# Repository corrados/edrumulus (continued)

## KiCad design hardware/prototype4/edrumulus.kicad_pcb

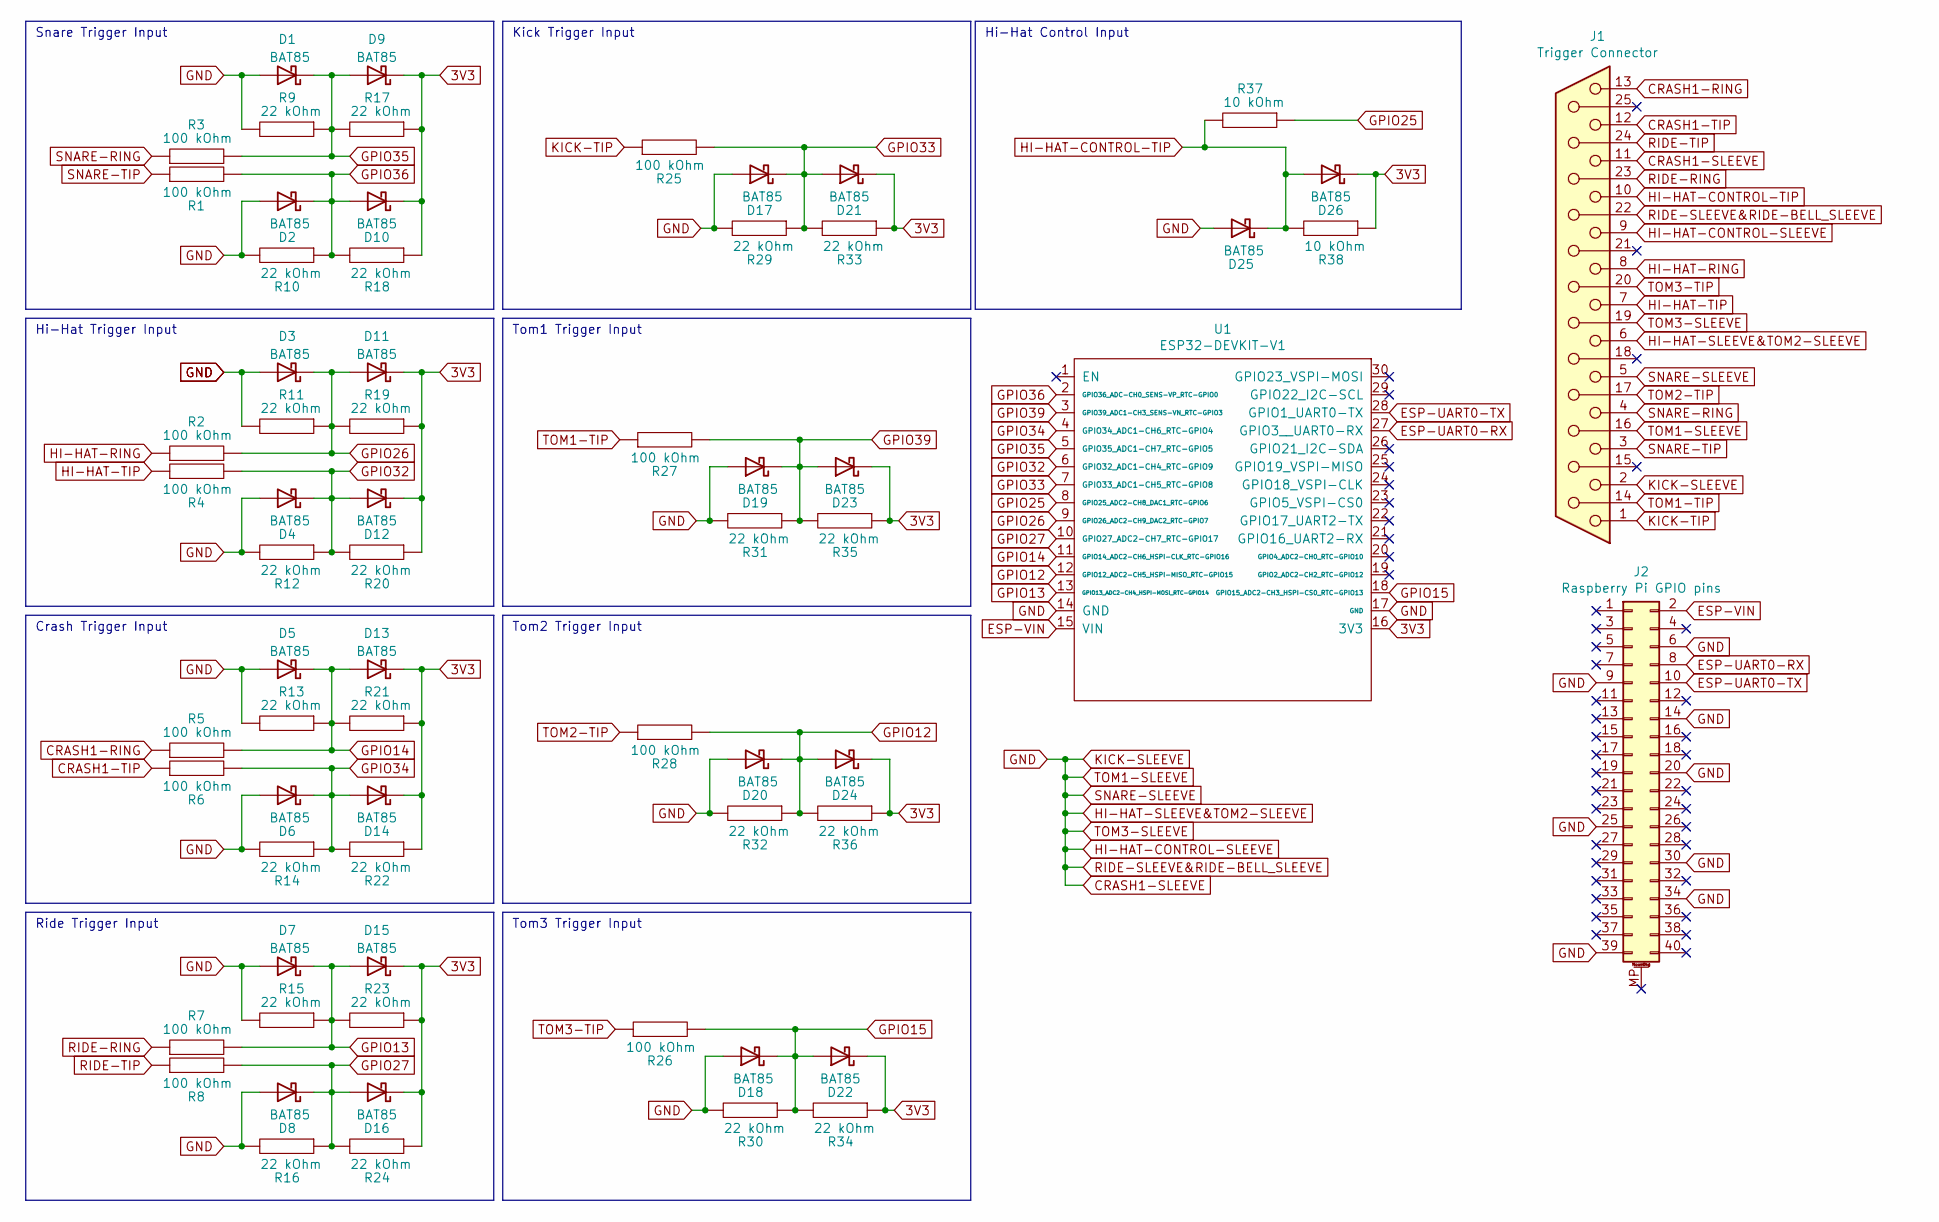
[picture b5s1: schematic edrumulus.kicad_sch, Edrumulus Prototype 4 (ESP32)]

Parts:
D1, D2, D3, D4, D5, D6, D7, D8, D9, D10, D11, D12, D13, D14, D15, D16, D17, D18, D19, D20, D21, D22, D23, D24, D25, D26: BAT85; D_MiniMELF
J1: Trigger Connector; DSUB-25_Female_Vertical_P2.77x2.84mm
J2: Raspberry Pi GPIO pins; PinHeader_2x20_P2.54mm_Vertical
R1, R2, R3, R4, R5, R6, R7, R8, R25, R26, R27, R28: 100 kOhm; R_1206_3216Metric_Pad1.30x1.75mm_HandSolder
R9, R10, R11, R12, R13, R14, R15, R16, R17, R18, R19, R20, R21, R22, R23, R24, R29, R30, R31, R32, R33, R34, R35, R36: 22 kOhm; R_1206_3216Metric_Pad1.30x1.75mm_HandSolder
R37, R38: 10 kOhm; R_1206_3216Metric_Pad1.30x1.75mm_HandSolder
U1: ESP32-DEVKIT-V1; esp32_devkit_v1

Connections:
3V3: D9.1 (K), D10.1 (K), D11.1 (K), D12.1 (K), D13.1 (K), D14.1 (K), D15.1 (K), D16.1 (K), D21.1 (K), D22.1 (K), D23.1 (K), D24.1 (K), D26.1 (K), R17.1, R18.1, R19.1, R20.1, R21.1, R22.1, R23.1, R24.1, R33.1, R34.1, R35.1, R36.1, R38.1, U1.16 (3V3)
CRASH1-RING: J1.13, R5.1
CRASH1-SLEEVE: D1.2 (A), D2.2 (A), D3.2 (A), D4.2 (A), D5.2 (A), D6.2 (A), D7.2 (A), D8.2 (A), D17.2 (A), D18.2 (A), D19.2 (A), D20.2 (A), D25.2 (A), J1.2, J1.5, J1.6, J1.9, J1.11, J1.16, J1.19, J1.22, J2.6, J2.9, J2.14, J2.20, J2.25, J2.30, J2.34, J2.39, R9.2, R10.2, R11.2, R12.2, R13.2, R14.2, R15.2, R16.2, R29.2, R30.2, R31.2, R32.2, U1.14 (GND), U1.17 (GND)
CRASH1-TIP: J1.12, R6.1
ESP-UART0-RX: J2.8, U1.27 (GPIO3__UART0-RX)
ESP-UART0-TX: J2.10, U1.28 (GPIO1_UART0-TX)
ESP-VIN: J2.2, U1.15 (VIN)
GPIO12: D20.1 (K), D24.2 (A), R28.2, R32.1, R36.2, U1.12 (GPIO12_ADC2-CH5_HSPI-MISO_RTC-GPIO15)
GPIO13: D7.1 (K), D15.2 (A), R7.2, R15.1, R23.2, U1.13 (GPIO13_ADC2-CH4_HSPI-MOSI_RTC-GPIO14)
GPIO14: D5.1 (K), D13.2 (A), R5.2, R13.1, R21.2, U1.11 (GPIO14_ADC2-CH6_HSPI-CLK_RTC-GPIO16)
GPIO15: D18.1 (K), D22.2 (A), R26.2, R30.1, R34.2, U1.18 (GPIO15_ADC2-CH3_HSPI-CS0_RTC-GPIO13)
GPIO25: R37.1, U1.8 (GPIO25_ADC2-CH8_DAC1_RTC-GPIO6)
GPIO26: D3.1 (K), D11.2 (A), R2.2, R11.1, R19.2, U1.9 (GPIO26_ADC2-CH9_DAC2_RTC-GPIO7)
GPIO27: D8.1 (K), D16.2 (A), R8.2, R16.1, R24.2, U1.10 (GPIO27_ADC2-CH7_RTC-GPIO17)
GPIO32: D4.1 (K), D12.2 (A), R4.2, R12.1, R20.2, U1.6 (GPIO32_ADC1-CH4_RTC-GPIO9)
GPIO33: D17.1 (K), D21.2 (A), R25.2, R29.1, R33.2, U1.7 (GPIO33_ADC1-CH5_RTC-GPIO8)
GPIO34: D6.1 (K), D14.2 (A), R6.2, R14.1, R22.2, U1.4 (GPIO34_ADC1-CH6_RTC-GPIO4)
GPIO35: D1.1 (K), D9.2 (A), R3.2, R9.1, R17.2, U1.5 (GPIO35_ADC1-CH7_RTC-GPIO5)
GPIO36: D2.1 (K), D10.2 (A), R1.2, R10.1, R18.2, U1.2 (GPIO36_ADC-CH0_SENS-VP_RTC-GPIO0)
GPIO39: D19.1 (K), D23.2 (A), R27.2, R31.1, R35.2, U1.3 (GPIO39_ADC1-CH3_SENS-VN_RTC-GPIO3)
HI-HAT-CONTROL-TIP: D25.1 (K), D26.2 (A), J1.10, R37.2, R38.2
HI-HAT-RING: J1.8, R2.1
HI-HAT-TIP: J1.7, R4.1
KICK-TIP: J1.1, R25.1
RIDE-RING: J1.23, R7.1
RIDE-TIP: J1.24, R8.1
SNARE-RING: J1.4, R3.1
SNARE-TIP: J1.3, R1.1
TOM1-TIP: J1.14, R27.1
TOM2-TIP: J1.17, R28.1
TOM3-TIP: J1.20, R26.1

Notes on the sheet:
Snare Trigger Input
Tom2 Trigger Input
Tom3 Trigger Input
Kick Trigger Input
Crash Trigger Input
Hi-Hat Trigger Input
Hi-Hat Control Input
Tom1 Trigger Input
Ride Trigger Input

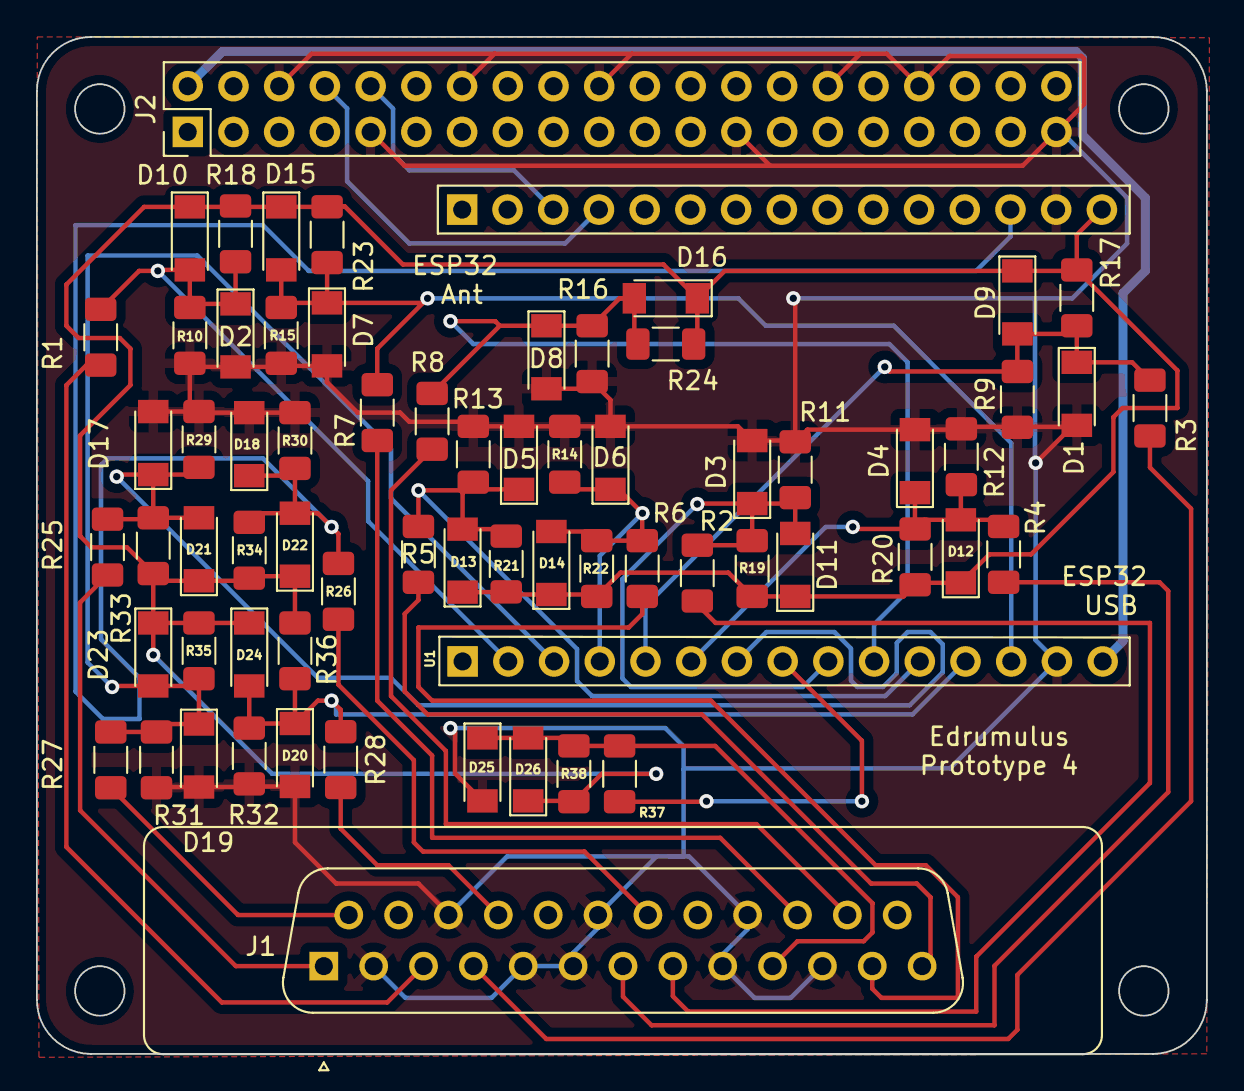
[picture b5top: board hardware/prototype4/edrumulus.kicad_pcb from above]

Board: 2 copper layers, 65.0 x 56.5 mm, 67 parts (0 on the bottom side), 31 nets.

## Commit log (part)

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2023-06-22 try to improve the clipping compensation algorithm -> improvement does not yet work correctly and needs to be fixed
2023-06-26 bug fix: fixed an out-of-bound read
2023-06-26 parameter update
2023-06-27 update: New case for prototype 5
2023-06-28 prepare for next version
2023-06-30 some fixes regarding the clipping compensation: enlarge overload history length (this is possible since we use a speed optimized FIFO now) and avoid modifying peak_delay
2023-06-30 added support for rim shot boost setting
2023-07-01 do log operation to calculate midi_pos when all detections done (at one place where also the log for velocity is calculated, too)
2023-07-01 code improvement and parameter adjustment
2023-07-01 introduce Erimstate for rim shot variable
2023-07-02 as a quick hack, re-use rim boost for new rim click treshold and use hi-hat open sound for rim click
2023-07-02 support midi note2 and midi note2 rim (needed for open hi-hat)
2023-07-03 small fixes with positional sensing
2023-07-04 move some text
2023-07-04 some cleanup
2023-07-04 prepare the get_midi_note function to cope with all rim shot enums (note that only the RIM_SHOT enum is actually implemented)
2023-07-08 speed optimization
2023-07-09 preparations for supporting a second rim switch
2023-07-12 move implementation of set_coupled_pad_idx in the cpp file
2023-07-12 introduce coupled_pad_idx_primary and change coupled_pad_idx to coupled_pad_idx_secondary
2023-07-15 finish fist untested version of set_coupled_pad_idx() function
2023-07-15 bug fix
2023-07-16 add support for the case "coupled_pad_idx_secondary < coupled_pad_idx_primary" (not yet tested)
2023-07-16 new setting: controller 120: pad coupling
2023-07-16 support new setting "coupling" in the GUI
2023-07-16 update documentation
2023-07-29 small fix for second rim
2023-07-29 make GUI mode the default for the run script
2023-08-05 added debug output for available heap as suggested in support forum
2023-08-06 added a comment and change a trigger setting
2023-08-12 platformio configuration added
    To build all boards, use: `pio run`
2023-08-12 platformio config: add missing teensy36
2023-08-12 CI: build all boards at once
    Since pio ci --board doesn't have any effect with a global
    config anyway, it makes sense to just build all boards
    at the same time.
2023-08-13 platformio config: use arduino-esp32 2.0.9
    https://github.com/espressif/arduino-esp32/issues/8471
2023-08-29 enable serial in addition to MIDI
2023-08-29 SDCARD_OUT: compile switch to write edrumulus signals to a SD card
    Signals are written to the SD card at a dedicated edrumulus directory.
    Files are rotated every minute to avoid data loss due to a power cycle.
    The output format is 16 Bit PCM wav, which is 4 Bits more than the
    format edrumulus uses (i.e. 20-30dB more than the maximum amplitude).
    This is mostly meant to help with debugging edrumulus to e.g. support
    new pads. It tends to be more realistic than the current test method,
2023-09-12 update manual according to recommendations in #93
2023-09-17 implement: Request Feature NoteOn instead of aftertouch #85
2023-09-17 code style
2023-09-25 support creating Drumgizmo kits with log-power values
2023-09-25 added raspi_optimized_drumkit flag
2023-09-26 revert last commit
2023-09-27 update trigger setting
2023-09-29 use different Drumgizmo configuration parameters
2023-09-29 adjust PearlMMX rock settings
2023-09-30 settings update
2023-09-30 adjusted trigger setting
2023-10-01 remove warning message since the problem in ESP32 Arduino library is now solved
2023-10-02 introduce controlthresh setting in MIDI XML file
2023-10-05 added sample shortening for Raspberry Pi usage and some other MIDI assignment optimizations
2023-10-05 use longer fade-out time and some code optimization/cleanup
2023-10-09 use correct pad type for the crash
2023-10-09 adjust CY8 thresh/sense values again
2023-10-12 Teensy 4.1: support ADC pins 14-17
    Fixes #102
2023-10-14 Teensy: use absolute pin numbers everywhere
2023-10-21 safety check added
    Check on edrumulus startup, if the ADCs roughly detect the expected
    1,65V from the voltage divider circuits. If not, abort and inform
    the user via serial console about the issue.
    The control port is skipped.
    This check may may detect:
    - incorrect analog circuits
2023-10-22 make dots more visibile on result plot
2023-10-24 in error case, let the board LED blink
2023-10-25 move definition of constant values in header and increase tolerated sampling rate offset from 100 Hz to 200 Hz
2023-10-25 specify constants in seconds, not in samples
2023-10-26 move the spike cancellation setting to the end of the list
2023-10-26 implement DC offset check inspired by Pull Request 107 by 3hhh
2023-11-01 show error state in GUI
2023-11-02 show type of error and in case of DC offset error, show pad/input information in the GUI
2023-11-04 hihat pedal: keep a history of 50 samples
    This gives users 50/8000/2 s = ~3ms to reach the pedal threshold.
    Previously it was ~0.6ms, which was unrealistically small.
    It made half-open hihat play possible on my hihat.
    Existing hihat control velocity thresholds & sensitivities may have
    to be lowered.
2023-11-04 mention Teensy 4.1 in README
2023-11-06 bug fix: use correct gradient calculation for pedal stomp detection (see discussion in Pull Request #110)
2023-11-07 use pos thres and pos sens for control pedal adjustments so that we can use the previous settings for the pedal stomp adjustment
2023-11-07 make the hi-hat pedal stomp parameters adjustable in the GUI with the thres and sense parameters
2023-11-07 added some comments
2023-11-08 improve rtmidi/teensy exception
2023-11-08 ignore .vscode/
2023-11-08 remove teensy specific exception
2023-11-08 settings change
2023-11-09 show status of trying to connect to Edrumulus device on edrumulus_gui startup
2023-11-11 add xtalk tool from 3hhh as a submodule in the tools directory
2023-11-11 adjust parameter to the new range
2023-11-11 add screenshot of windows setup (#115)
2023-11-11 show python version and os in gui
2023-11-11 doc: add link to manual
2023-11-12 added gallery file
2023-11-12 added link to gallery
2023-11-12 add ryanalexmartin prototype in gallery
2023-11-12 pad types are now sorted in a meaningful order in the GUI with additional information
2023-11-12 fix for LCD GUI
2023-11-12 text updates
2023-11-13 fix volume issue with ecasound kits in edrumulus_gui
2023-11-13 introduce function ecasound_apply_kit_volume() in edrumulus_gui
2023-11-15 support MPS 750x pads (excl. hihat) & Lemon LEHHS12C
2023-11-18 remove link to project which is very old and not maintained anymore
2023-11-26 initial implementation of ESP32 direct serial communication
2023-11-27 fix typo
2023-11-27 suppress ALSA warning messages showing up in the GUI
2023-11-28 support serial device setting via command line
2023-11-29 GUI: use the MIDI notes provided in the settings
2023-11-29 move settings file names to the beginning of the file
2023-11-29 set MIDI notes to 0 per default (needed for midi map generation in the GUI)
2023-11-29 fix issue with cymbal choke not working anymore (MIDI note 0 is used to select a different aftertouch method)
2023-11-30 bug fix: go back to original version with import of rtmidi midiutil library
2023-11-30 some fixes for Windows serial
2023-11-30 finish first pytemidi implementation for Windows serial which works
2023-12-01 put imports in one line
2023-12-02 small change
2023-12-02 small fix
2023-12-16 ESP32-S3 has been tested with front end and it works
2023-12-29 TEST only show peaks and remove samples in between
2023-12-30 update manual
2023-12-31 initial support for positional sensing for rim shots
2023-12-31 added rim positional sensing parameters to the GUI
2024-01-05 added default parameters for rim shot positional sensing for PD120
2024-01-07 update change log and trigger settings
2024-01-07 2023 -> 2024
2024-02-29 generic CFG_TUSB_CONFIG_FILE path
2024-03-03 EEPROM -> Preferences for ESP32
2024-03-04 preferences_settings -> settings
2024-03-06 Use latest realeases
2024-04-13 bug fix with lcdgui mode in run_edrumulus.sh
2024-04-19 support kit/volume in webui
2024-04-24 re-sort trigger parameters sets
2024-04-24 remove comment which does not apply anymore
2024-04-25 rename flash binary to edrumulus.ino.bin
2024-04-25 update gitignore to ignore ESP32 flash binary
2024-06-05 introduce new files edrumulus_signalprocessing.cpp/.h
2024-06-07 code style fixes
2024-06-08 fix deprecated warnings
2024-06-08 create function calculate_subsample_peak_value
2024-06-08 create function overload_correction
2024-06-09 test patch
2024-06-09 now it compiles for new ESP32 library but does not yet work (reboots)
2024-06-11 fix crashes under IDF V3.x
2024-06-12 move cancel_ADC_spikes function in Edrumulus class
2024-06-14 remove redundant setting
2024-06-14 MIDI Library is already added in env section
2024-06-14 remove MIDI library version requirement
2024-06-14 try to fix issue
2024-06-14 add initial clang format configuration file
2024-06-14 apply clang format
2024-06-15 add clang format check in the Github pipeline
2024-06-15 use IndentPPDirectives: AfterHash
2024-06-15 small change to test pull request rules working
2024-06-15 prepare for merge from main
2024-06-15 added some test code which uses settings.end()
2024-06-19 remove redundant entries for clang format configuration
2024-07-16 use AlignAfterOpenBracket: Align for clang format
2024-07-18 Hihat pedal: only trigger when it's absolutely closed
    This makes pedal stomps caused by half-open hihat play less likely.
    Also increase the various hihat ranges so that they can be used more
    easily.
    Fixes #145
2024-08-12 remove deprecated function of ESP32-S3
2024-12-15 changes for Raspberry Pi 4 prototype
2025-03-22 Millenium HD-120 support
    Add support for the [Millenium HD-120](https://www.thomann.co.uk/millenium_hd_120_9_cymbal_pad.htm)
    9" cymbal, which is small and cheap.
2025-04-02 fix clang format configuration
2025-04-03 try to remove tiny usb library
2025-04-03 add workflow_dispatch
2025-05-04 did not work :-(
2025-05-04 next try
2025-05-17 manual: fix: shorting cannot break the ADC
2025-05-30 re-sorting
2025-11-04 update gallery with 3hhh pictures
2025-11-28 show Edrumulus version in webui mode
2025-12-06 go back to original jack parameters on Raspberry
2025-12-06 pi4 update
2025-12-07 fix for rasperry pi 4
2025-12-07 go back to original trigger settings
2025-12-07 set VH12
2025-12-27 adjust levels for rock kit
2025-12-27 increase level of both Pearl MMX kits in ecasound
2025-12-27 add another 2 dB to natural kit
2025-12-31 preparations for load indicator
2025-12-31 some more work for load indicator (not yet working correctly)
2025-12-31 load in percent
2025-12-31 fixes and clean up
2025-12-31 test code for checking delay in capture samples function on ESP32
2025-12-31 remove test code
2025-12-31 improve help output
2026-01-01 use consistent sample type (unit16_t)
2026-01-01 introduce cur_dc_offset
2026-01-01 if dc_offset_iir_gamma is double, a type conversion is no longer needed
2026-01-01 speed optimize update_fifo function
2026-01-01 2026
2026-01-01 testing sum function -> seems to be slower than original code
2026-01-01 try out introducing cur_prev[x]_input_state -> does not give speed improvement
2026-01-01 go back to original code
2026-01-01 i++ for consistency with other source code
2026-01-03 remove LCD GUI support
2026-01-03 tom1 setting change
2026-01-04 added test code
2026-01-04 add initial support for crash2 input
2026-01-04 test platformio S3
2026-01-04 add analogbetateam prototype to gallery
2026-01-04 fix picture size
2026-01-07 consider crash2 for prototype 5
2026-01-08 fix equations in algorithm.md
2026-01-08 add test code for FFT evaluation
2026-01-09 add new link
2026-01-12 move capture_samples files in subdirectory so that they can be opened in Ardunio IDE
2026-01-14 create macro DBG_FCT_OCTAVE_SAMPLE_IMPORT_EXPORT
2026-01-14 testing capturing buffered samples
2026-01-14 longer buffer
2026-01-15 increase recording length
2026-01-16 code improvement
2026-01-20 optionally, post process recorded data
2026-01-21 move capture_samples to misc directory
2026-01-21 clean up
2026-01-21 disable debugging
